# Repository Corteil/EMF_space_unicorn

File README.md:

# 🦄 Space Unicorn — EMF 2026 Hexpansion

A WS2812 NeoPixel hexpansion for the EMF Tildagon badge. An ATtiny85 setup as an I²C client
drives the LEDs with animated patterns, predefined colour palettes and a user
button for live pattern cycling. Settings can be saved to the ATtiny85's
internal EEPROM so the badge lights up on its own, without the control app.
This repository holds the firmware and the KiCad hardware design.

| Front | Rear |
|:-----:|:----:|
|  |  |

---

## Project links

The Space Unicorn is an EMF 2026 hexpansion — an ATtiny85 driving WS2812
NeoPixels, controlled over I²C from a Tildagon badge.

- 🦄 **Tildagon control app** — drive patterns, palettes, colour and speed from
  the badge: <https://github.com/Corteil/tildagon-space-unicorn>
- 📟 **This repo** — firmware (root) and the KiCad PCB design
  ([`hardware/`](hardware/)).
- 📇 **EMF hexpansion registry** — VID `0x1969` / PID `0x5355`, for OTA firmware:
  <https://github.com/emfcamp/hexpansion-firmwares/tree/main/0x1969/0x5355>

---

## Hardware

The full KiCad design (schematic, board, footprint libraries, gerbers and
renders) is in [`hardware/`](hardware/).

ATtiny85 pin assignments:

| Pin | Port     | Function                                      |
|-----|----------|-----------------------------------------------|
| 1   | PB5/RESET| Reset button                                  |
| 2   | PB3      | NeoPixel data output                          |
| 3   | PB4      | User button (active-low, internal pull-up)    |
| 4   | GND      |                                               |
| 5   | PB0      | I2C SDA                                       |
| 6   | PB1      | Heartbeat LED (1 Hz blink; flashes on I2C data)|
| 7   | PB2      | I2C SCL                                       |
| 8   | VCC      |                                               |

### Circuit

```
                        ^ VCC
                        |
    +--------+----------+----------+-----+-------+
    |        |                     |     |       |
    |       |"| 10k                |     |       |
    |       |_|                   |"| 10k |"| 10k
    |        |   +--ATtiny85--+   |_|   |_|
    |        +---| Reset  Vcc |----+     |
    |            |            |          |
  _____ 0.1u     |        SCL |----------+-------<> SCL
  _____  ,-------| GND    SDA |------------------<> SDA
    |    |       +------------+
    |    v GND
    |
    +---------------------------------------------------> NeoPixel Data (PB3)
    |
    +--[ button ]-- GND                                   User button (PB4)
    |
    +--[ LED ]--[ 330R ]-- GND                            Heartbeat LED (PB1)
```

Pull-ups: 10 kΩ on SCL, SDA and RESET to VCC.

---

## Building

Requires `avr-gcc`, `avr-libc`, and `avrdude`.

```bash
sudo apt install gcc-avr avr-libc binutils-avr avrdude

git clone --recurse-submodules https://github.com/Corteil/EMF_space_unicorn
cd EMF_space_unicorn

make fuses  # MUST be run once on any new or replacement chip
make        # build and flash
```

The default programmer is **Atmel-ICE (ISP)**. To use a different programmer
edit the top of `Makefile`:

```makefile
AVRDUDE_PROGRAMMER = usbasp     # or linuxspi, avrisp2, usbtiny, ...
AVRDUDE_PORT       = usb
```

Build artifacts (`main.hex`, `main.elf`) are not tracked in the repository —
always build from source so the hex matches the current code.

### Fuses — required on every fresh chip

> **Important:** ATtiny85 chips ship from the factory with `CKDIV8` programmed,
> running the CPU at 1 MHz. The WS2812 driver requires exactly 8 MHz. With the
> wrong clock the NeoPixels will be **stuck solid white** and the button will be
> unresponsive.
>
> Run `make fuses` once whenever fitting a new or replacement chip. This sets
> `LFUSE=0xE2` (8 MHz internal RC, no divider) and is safe to re-run on a
> chip that is already correctly programmed.

---

## Flash and RAM usage

| Section | Used    | Available |
|---------|---------|-----------|
| Flash   | 3708 B  | 8192 B    |
| RAM     | 390 B   | 512 B     |

---

## I2C Protocol

**Slave address: 0x40** (hardcoded in `i2c/i2c_slave_defs.h`)

The full 8-bit register space (0x00–0xFF) is addressable.

Write transaction:

| Start | Addr (0x40) | Register | Data bytes… | Stop |

Read transaction:

| Start | Addr (0x40) | Register | Restart | Addr (0x41) | Data bytes… | Stop |

The register address auto-increments after each byte, so multi-byte reads and
writes are supported in a single transaction.

**LED values are updated only after a STOP condition is received.** There is
no per-LED frame buffer — each pixel is computed on the fly as the WS2812
stream is clocked out, so LED count is limited by power and frame rate, not
by RAM.

---

## Register Map

| Address     | Name           | Description                                    | Reset |
|-------------|----------------|-------------------------------------------------|-------|
| 0x00        | **CTRL**       | Control register                                | 0x00  |
| 0x01        | **PATTERN**    | Pattern ID (0–10, see table below)              | 0x01  |
| 0x02        | **SPEED**      | Ticks per animation frame (1=fast, 255=slow)    | 0x0A  |
| 0x03        | **FALLBACK**   | Pattern ID run on boot / after an idle timeout  | 0x07  |
| 0x04        | **N_LEDS_LO**  | Active LED count, low byte                      | 0x40  |
| 0x05        | **N_LEDS_HI**  | Active LED count, high byte                     | 0x00  |
| 0x06        | **N_COLS**     | Matrix columns for RAINBOW_MTX (0 ⇒ 8)          | 0x08  |
| 0x07        | **IDLE_TO**    | Inactivity timeout in seconds before reverting to FALLBACK (0=off) | 0x00 |
| 0x08        | **PARAM1**     | Pattern-specific parameter                      | 0x01  |
| 0x09        | **PARAM2**     | Pattern-specific parameter                      | 0x05  |
| 0x0A        | **PAL_SEL**    | Palette selector (0=user, 1–7=predefined)       | 0x00  |
| 0x10        | **GLB_G**      | Primary colour — green                          | 0x00  |
| 0x11        | **GLB_R**      | Primary colour — red                            | 0xFF  |
| 0x12        | **GLB_B**      | Primary colour — blue                           | 0x00  |
| 0x13        | **SEC_G**      | Secondary colour — green                        | 0x00  |
| 0x14        | **SEC_R**      | Secondary colour — red                          | 0x00  |
| 0x15        | **SEC_B**      | Secondary colour — blue                         | 0x00  |
| 0x20–0x4F   | **PALETTE[0–15]** | 16-entry user colour palette, 3 bytes (G,R,B) each | 0x00 |
| 0x50–0xFF   | **INDEX[0–351]**  | Packed 4-bit palette-index buffer for matrix mode (see below) | 0x00 |

`N_LEDS_LO`/`N_LEDS_HI` form a 16-bit active LED count (little-endian); a
value of 0 is treated as 64. `PATTERN`, `SPEED`, `PARAM1`/`PARAM2` and colours
are unchanged in meaning from earlier firmware, but have moved address.

> WS2812 byte order on the wire is **G, R, B**.

---

## CTRL Register (0x00)

| Bit | Name       | Description |
|-----|------------|-------------|
| 0   | **RST**    | Write 1 to reset all registers to defaults. Auto-clears. |
| 1   | **GLB**    | Write 1 to display the primary colour (GLB_G/R/B) on all LEDs. |
| 2   | **PAT_EN** | Write 1 to enable the pattern animation engine. |
| 3   | **IDX_EN** | Write 1 to stream LED colours from the packed index buffer (0x50–0xFF) instead of a pattern. |
| 4   | **SAVE**   | Write 1 to persist the current configuration to EEPROM. Auto-clears once saved. |
| 7–5 | —          | Reserved, read as 0. |

---

## Patterns (REG_PATTERN, 0x01)

| ID | Name            | Description                                                   | Uses |
|----|-----------------|---------------------------------------------------------------|------|
| 0  | OFF             | All LEDs off                                                  | —           |
| 1  | SOLID           | All LEDs show primary colour                                  | —           |
| 2  | CHASE           | Scrolling comet; tail dims by right-shift, capped at 1/128    | PARAM1 = tail length |
| 3  | BLINK           | All LEDs toggle between primary and off                       | —           |
| 4  | ALTERNATE       | Even LEDs = primary, odd = secondary; swaps each frame        | —           |
| 5  | WIPE            | Fill left→right one LED per frame, then clear                 | —           |
| 6  | TWINKLE         | Independently-timed sparkles fade in/out at random LEDs       | PARAM1 = number of simultaneous sparkles (max 8) |
| 7  | RAINBOW         | Full hue wheel cycling across the strip                       | PARAM2 = hue step per LED |
| 8  | RAINBOW_MTX     | Diagonal rainbow on an N_COLS-wide grid, rotates over time     | PARAM1 bit 0 = serpentine wiring |
| 9  | RETRO_BLINK     | Random LEDs toggle independently (50s computer effect); state kept for the first 512 LEDs only | PARAM1 = LEDs toggled per frame (max 8) |
| 10 | LARSON          | Cylon/KITT scanner; bright eye bounces end-to-end, tail dims same as CHASE | PARAM1 = tail length |

Enable a pattern by writing PAT_EN to CTRL and the ID to PATTERN. The user
button (PB4) also cycles through patterns 1–10 with a single press.

---

## Predefined Palettes (REG_PAL_SEL, 0x0A)

Writing a palette ID loads predefined primary and secondary colours from flash
(PROGMEM) into GLB and SEC registers. Writing 0 keeps the current user colours.

| ID | Name    | Primary (G R B)   | Secondary (G R B) |
|----|---------|-------------------|-------------------|
| 0  | USER    | *(unchanged)*     | *(unchanged)*     |
| 1  | FIRE    | 100, 255, 0       | 0, 128, 0         |
| 2  | OCEAN   | 255, 0, 255       | 0, 0, 64          |
| 3  | FOREST  | 200, 50, 0        | 48, 10, 0         |
| 4  | PARTY   | 0, 255, 0         | 0, 0, 255         |
| 5  | MONO_W  | 255, 255, 255     | 32, 32, 32        |
| 6  | RAINBOW | 0, 255, 0         | 0, 0, 255         |
| 7  | HEAT    | 0, 255, 0         | 200, 255, 0       |

---

## User Palette and Index Buffer (matrix mode)

Setting `CTRL_IDX_EN` switches LED output from the pattern engine to a
directly-addressable canvas, driven by two blocks:

- **`PALETTE[0–15]`** (0x20–0x4F) — 16 user-defined colours, 3 bytes (G, R, B)
  each. On reset, entries 0 and 1 are set to the primary/secondary colours;
  all 16 entries can be freely overwritten over I2C.
- **`INDEX[0–351]`** (0x50–0xFF) — one 4-bit palette index per LED, two LEDs
  packed per byte (LED *n*'s index is the low nibble of byte `n/2` if *n* is
  even, the high nibble if odd). Index **0 always renders as off/blank**,
  regardless of palette contents; indices 1–15 select `PALETTE[1]`…`PALETTE[15]`.

Index mode is bounded by the size of the index buffer: 176 bytes × 2 LEDs per
byte = **352 LEDs maximum**, irrespective of `N_LEDS`.

---

## Persistence, Fallback and Idle Timeout

- **Save**: writing `CTRL_SAVE` copies the control/colour registers and the
  16-entry user palette into the ATtiny85's internal EEPROM. The bit
  auto-clears once the save completes.
- **Boot**: on power-up, a valid saved configuration is reloaded; otherwise
  firmware defaults are used. The badge then runs the `FALLBACK` pattern
  immediately, so it lights up without the control app.
- **Idle timeout**: if `IDLE_TO` is non-zero and no I2C write is seen for that
  many seconds, the firmware reverts to the `FALLBACK` pattern.

---

## Heartbeat LED (PB1)

The LED on PB1 serves two purposes:

- **Heartbeat**: slow blink while the firmware is running, driven by Timer0 ISR.
- **Data activity**: overrides the heartbeat with a brief solid-on flash each
  time an I2C STOP condition is received.

---

## Testing

`test_registers.py` is a MicroPython / Raspberry Pi dual-platform test tool
that verifies all registers over I2C.

**Raspberry Pi (Linux):**
```bash
sudo apt install python3-smbus2
python3 test_registers.py
```

**Pi Pico (MicroPython):**
```
# Copy test_registers.py to the Pico, then run from the REPL or Thonny.
# Edit MP_PIN_SDA / MP_PIN_SCL at the top of the file to match your wiring.
mpremote run test_registers.py
```

The tool provides an interactive menu for running automated register tests and
live control of patterns, palettes, colours, and individual LEDs.

---

## Acknowledgements

This firmware extends
[neopixel_i2c](https://github.com/usedbytes/neopixel_i2c) by
**Brian Starkey (usedbytes)**, which provides the USI I2C slave implementation
and the original WS2812 driving code. The WinAVR Makefile was written by
**Eric B. Weddington, Jörg Wunsch et al.** and modified by **Elliot Williams**.
The [light_ws2812](https://github.com/cpldcpu/light_ws2812) library by
**cpldcpu** is used for WS2812 output.

---

---

# Original README — neopixel_i2c (picopixel)

> The following is the original README from the upstream neopixel_i2c project
> by Brian Starkey (usedbytes), preserved for reference.

This is an AVR-based neopixel driver. It accepts commands over i2c to drive a
a number of ws2812 LED pixels.

The code on the master branch is set up for an Attiny85, with the LEDs on PB3,
using an usbasp programmer. The fuses should be set to use 8 MHz internal
oscillator, **no divider**

## How many LEDs?
The number of LEDs is currently hardcoded in the firmware. The maximum number
depends on the amount of RAM available on your AVR.
An Attiny45 should be able to drive 82 LEDs, and an Attiny85, 167.

## Circuit

Suggested circuit.

```
                            ^ VCC
                            |
    +--------+--------------+-------------+-----+-------+
    |        |                            |     |       |
    |       |"| 10k                       |     |       |
    |       |_|                           |     |       |
    |        |     +Attinyx5--------+     |    |"| 2k2 |"| 2k2
    |        +-----| Reset      Vcc |-----'    |_|     |_|
    |              |                |           |       |
  _____ 0.1u       |                |           |       |
  _____  ,---------|            SCL |-----------+-------|-----<> SCL
    |    |         |                |                   |
    |    |         |                |                   |
    |    |       --|                |--                 |
    |    |         |                |                   |
    |    |         |                |                   |
    +----|---+-----| GND        SDA |-------------------+-----<> SDA
         |   |     +----------------+
         |   v GND
         |
         '-----------------------------------------------------> NeoPixel Data

```

## Getting the code

This project uses git submodules (I kinda wish it didn't...). You can clone
it like so:

```git clone --recursive https://github.com/usedbytes/neopixel_i2c```

If your git version is too old to support that, do this instead:

```
git clone --recursive https://github.com/usedbytes/neopixel_i2c
cd neopixel_i2c
git submodule update --init --recursive
```

## Basic Functionality

There are two basic operating modes:
 * In *normal* mode, each LED is individually driven based on the value in its
   control register.
 * In *global* mode, all LEDs are driven to the same value, based on the values
   in the global value registers.

The operating modes are selected by flipping the *GLB* bit in the **CTRL**
register.

## i2c Protocol

**The slave address is currently hardcoded to 0x40 in the firmware**, see

```
i2c/i2c_slave_defs.h:30
```

This utilises my i2c slave library (https://github.com/usedbytes/usi_i2c_slave)
which means it follows a fairly standard i2c protocol (for more, see here:
http://www.robot-electronics.co.uk/i2c-tutorial).

Writes look like this:

| Start | Slave Address << 1 | Register Address | Data | Stop |
|-------|--------------------|------------------|------|------|

The register address will auto-increment after every byte, so you can write
data in bursts.

Reads look like this:

| Start | Slave Address | Register Address | Restart | (Slave Address << 1) + 1  | Data | Stop |
|-------|---------------|------------------|---------|---------------------------|------|------|

First you do a write transaction to set the register address to read from, then
a read transaction to read the data. When you've read all the data you want,
send a NAK after the last byte to terminate the read.

**The LED values are only updated after a STOP is received**

## Register Map
The register map consists of a number of global control registers - address
0x0-0x3 - followed by an array of registers which hold the individual value
for each LED in normal mode.

| **Address** | **Name**     | **Description**      | **Access** | **Reset** |
|------------:|--------------|:---------------------|--------|------:|
|   0x00      | **CTRL**     | Control Register     | R/W    |    0  |
|   0x01      | **GLB_G**    | Global Green Value   | R/W    |    0  |
|   0x02      | **GLB_R**    | Global Red Value     | R/W    |    0  |
|   0x03      | **GLB_B**    | Global Blue Value    | R/W    |    0  |
|Array follows|--------------|----------------------|--------|-------|
|   0x04      | **GREEN[0]** | Green value, LED0    | R/W    |    0  |
|   0x05      | **RED[0]**   | Red value, LED0      | R/W    |    0  |
|   0x06      | **BLUE[0]**  | Blue value, LED0     | R/W    |    0  |
|   ....      | ....         | ....                 | ....   | ....  |
| (3*n) + 4   | **GREEN[n]** | Green value, LEDn    | R/W    |    0  |
| (3*n) + 5   | **RED[n]**   | Red value, LEDn      | R/W    |    0  |
| (3*n) + 6   | **BLUE[n]**  | Blue value, LEDn     | R/W    |    0  |

## Register Descriptions

### **CTRL**
The control register sets the operating mode.

|   Name: | RSVD | RSVD | RSVD | RSVD | RSVD | RSVD | GLB  | RST  |
|--------:|:----:|:----:|:----:|:----:|:----:|:----:|:----:|:----:|
|    Bit: |    7 |    6 |    5 |    4 |    3 |    2 |    1 |    0 |
| Access: |    r |    r |   r  |   r  |   r  |   r  |  rw  |  rw  |

#### *RST*
Writing a 1 to this bit will reset the LED controler, setting all LEDs to OFF

This bit will be automatically cleared once the reset has completed.

#### *GLB*
Writing a one to this bit causes the global color value to be displayed on all
LEDs at the end of the transaction - Normally you would set the **GLB_R**,
**GLB_G**, and **GLB_B** values in the same transaction as setting the *GLB*
bit so that the new colour is immediately applied.

Writing a zero to this bit will disable the global colour override and return to
normal operation.

### **GLB_R**, **GLB_G**, **GLB_B**
These registers hold the global colour value. When the *GLB* bit in the
**CTRL** register is set, all LEDs will display this colour.

### **LED Value Array**
Everything after the global registers is an array of data for each LED.
When the *GLB* bit is not set, each LED will display whatever value is
programmed in its corresponding register set.

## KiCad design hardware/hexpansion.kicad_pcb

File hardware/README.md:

# Space Unicorn — hardware

KiCad design files for the EMF26 Space Unicorn hexpansion.

| Front | Rear |
|:-----:|:----:|
|  |  |

## Contents

| Path | What |
|------|------|
| `hexpansion.kicad_pro` / `.kicad_sch` / `.kicad_pcb` | KiCad project, schematic and board. |
| `fp-lib-table`, `sym-lib-table` | Library tables. |
| `*.pretty/` | Project-local footprint libraries (`unicorn`, `heart`, `gfx`, `NextPCB`). |
| `gerbers/` | Gerbers + drill files for fabrication. |
| `renders/` | Board renders and the paper template. |
| `LICENSE.txt` | Hardware licence. |

## Notes

- The board carries an **ATtiny85** (WS2812 driver, I²C `0x40`), an **M24256E**
  EEPROM (hexpansion identity + resident app), and a **BC857BS** for Ext_5V
  reverse-feed protection.
- `fp-lib-table` references some footprints by absolute local paths (parts from
  `…/Hardware/parts/…`) and a sibling `tildagon-base`. These won't resolve on a
  fresh clone, but KiCad **caches footprints in the `.kicad_pcb`**, so the board
  opens, views and plots correctly. Re-point those library entries if you need to
  edit footprints.

## Related

- Firmware: this repository's root.
- Tildagon control app: <https://github.com/Corteil/tildagon-space-unicorn>

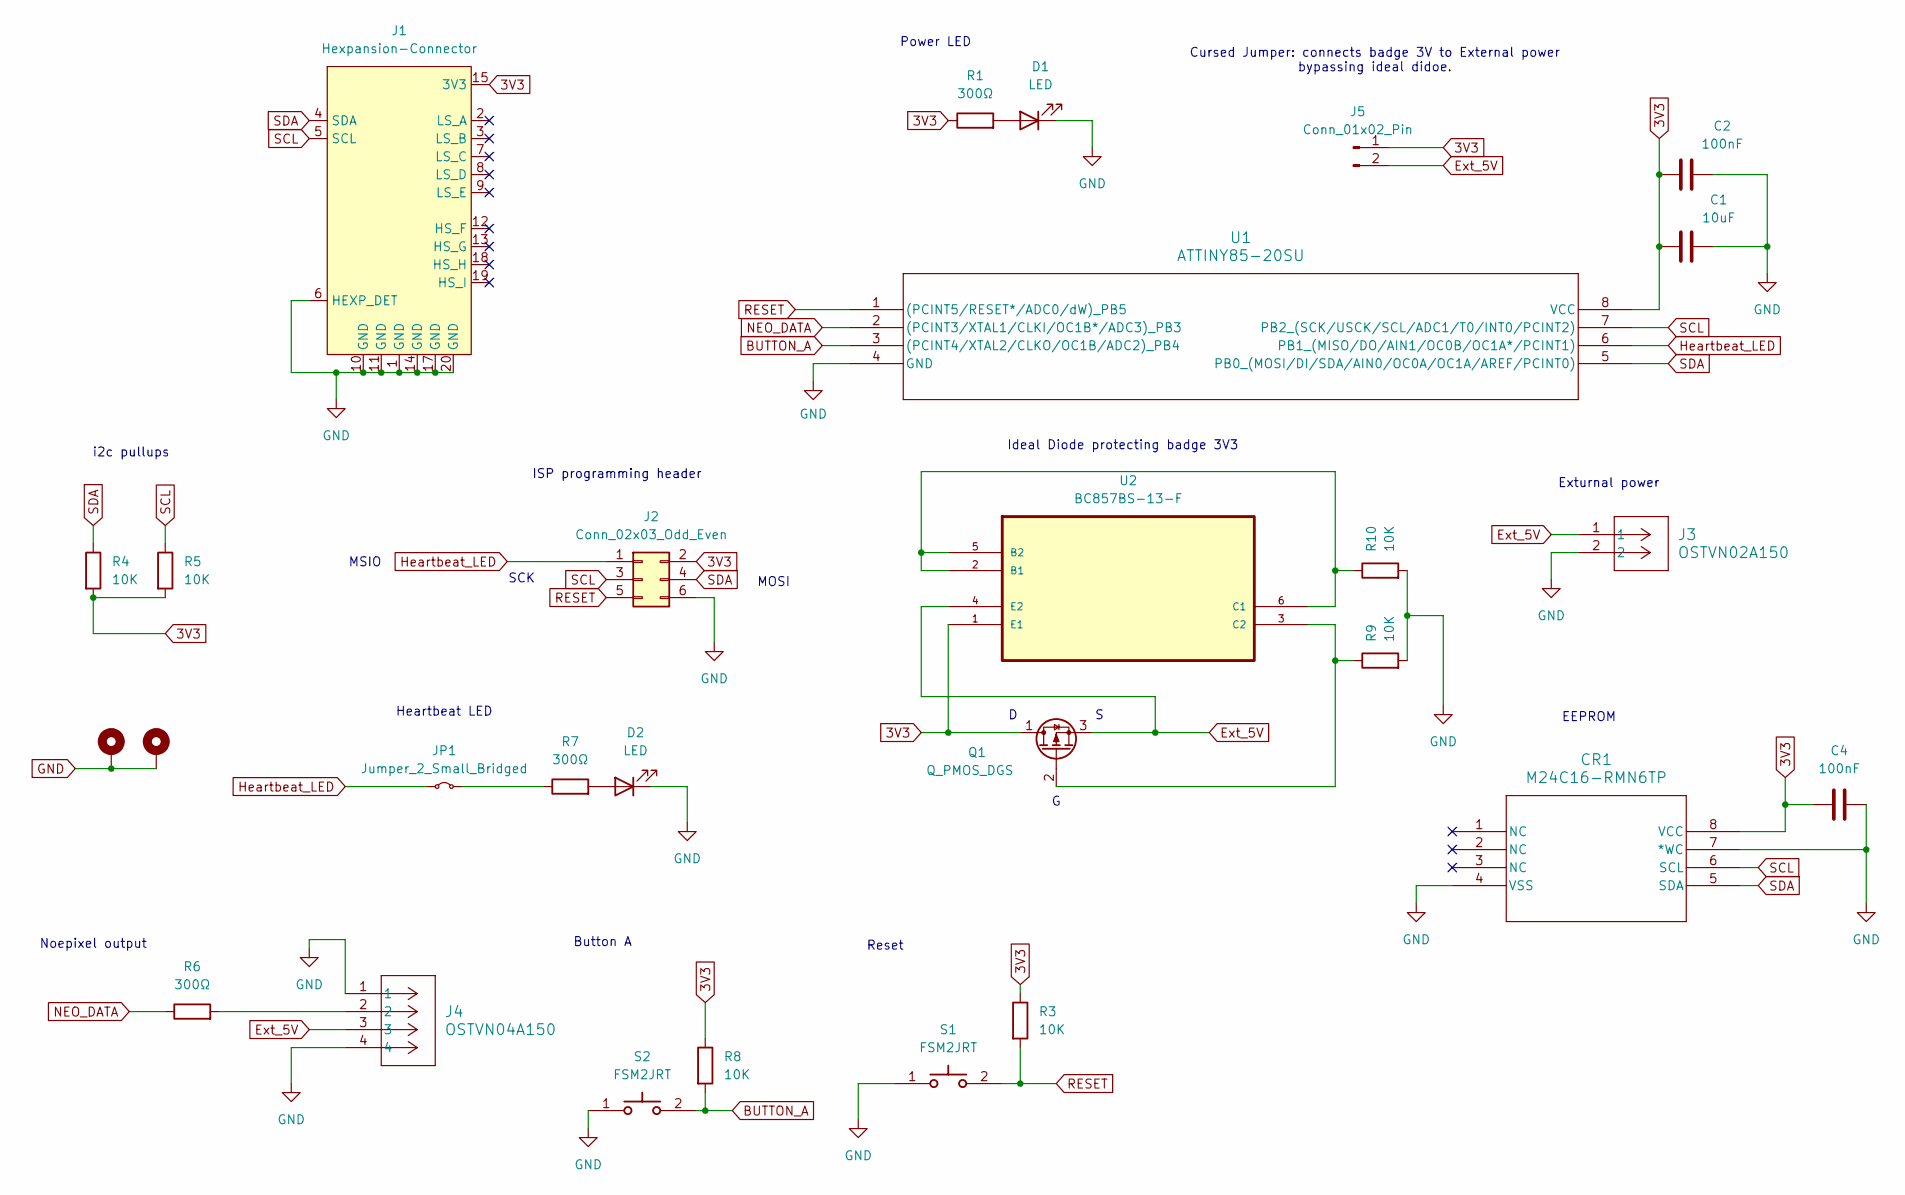
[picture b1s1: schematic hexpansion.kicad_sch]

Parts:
C1: 10uF; C_0603_1608Metric_Pad1.08x0.95mm_HandSolder
C2, C4: 100nF; C_0603_1608Metric_Pad1.08x0.95mm_HandSolder
CR1: M24C16-RMN6TP; SO-8_STM
D1, D2: LED; LED_0805_2012Metric
H1, H2: MountingHole_Pad; MountingHole_2.2mm_M2_Pad_Via
J1: Hexpansion-Connector; hexpansion-edge-connector
J2: Conn_02x03_Odd_Even; PinHeader_2x03_P2.54mm_Vertical
J3: OSTVN02A150; CONN_OSTVN02A150_OST
J4: OSTVN04A150; CONN_OSTVN04A150_OST
J5: Conn_01x02_Pin; PinHeader_1x02_P2.54mm_Vertical
JP1: Jumper_2_Small_Bridged; SolderJumper-2_P1.3mm_Bridged2Bar_RoundedPad1.0x1.5mm
Q1: Q_PMOS_DGS; SOT-23
R1, R6, R7: 300Ω; R_0603_1608Metric
R3, R4, R5, R8, R9, R10: 10K; R_0603_1608Metric
S1, S2: FSM2JRT; Manufacturer_Part_Number FSM2JRT
U1: ATTINY85-20SU; 8S2_ATM
U2: BC857BS-13-F; SOT65P210X100-6N; MPN BC857BS-13-F

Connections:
3V3: C1.1, C2.1, C4.1, CR1.8 (VCC), J1.15 (3V3), J1.16 (3V3), J2.2, J5.1, Q1.1 (D), R1.1, R3.1, R4.2, R5.2, R8.1, U1.8 (VCC), U2.1 (E1)
BUTTON_A: R8.2, S2.2 (NO), U1.3 ((PCINT4/XTAL2/CLKO/OC1B/ADC2)_PB4)
Ext_5V: J3.1, J4.3, J5.2, Q1.3 (S), U2.4 (E2); also elsewhere on the board
GND: C1.2, C2.2, C4.2, CR1.4 (VSS), CR1.7 (*WC), D1.1 (K), D2.1 (K), H1.1 (1_1), H2.1 (1_1), J1.1 (GND), J1.6 (HEXP_DET), J1.10 (GND), J1.11 (GND), J1.14 (GND), J1.17 (GND), J1.20 (GND), J2.6, J3.2, J4.1, J4.4, R9.2, R10.2, S1.1 (COM), S2.1 (COM), U1.4 (GND); also elsewhere on the board
Heartbeat_LED: J2.1, JP1.1 (A), U1.6 (PB1_(MISO/DO/AIN1/OC0B/OC1A*/PCINT1))
NEO_DATA: R6.1, U1.2 ((PCINT3/XTAL1/CLKI/OC1B*/ADC3)_PB3)
unnamed: D1.2 (A), R1.2
unnamed: D2.2 (A), R7.2
unnamed: J4.2, R6.2
unnamed: JP1.2 (B), R7.1
unnamed: Q1.2 (G), R9.1, U2.3 (C2)
unnamed: R10.1, U2.2 (B1), U2.5 (B2), U2.6 (C1)
RESET: J2.5, R3.2, S1.2 (NO), U1.1 ((PCINT5/RESET*/ADC0/dW)_PB5)
SCL: CR1.6 (SCL), J1.5 (SCL), J2.3, R5.1, U1.7 (PB2_(SCK/USCK/SCL/ADC1/T0/INT0/PCINT2))
SDA: CR1.5 (SDA), J1.4 (SDA), J2.4, R4.1, U1.5 (PB0_(MOSI/DI/SDA/AIN0/OC0A/OC1A/AREF/PC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)

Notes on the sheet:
Power LED
Exturnal power
Heartbeat LED
Noepixel output
MSIO
EEPROM
MOSI
ISP programming header
SCK
Reset
Button A
Cursed Jumper: connects badge 3V to External power bypassing ideal didoe.
Ideal Diode protecting badge 3V3
i2c pullups

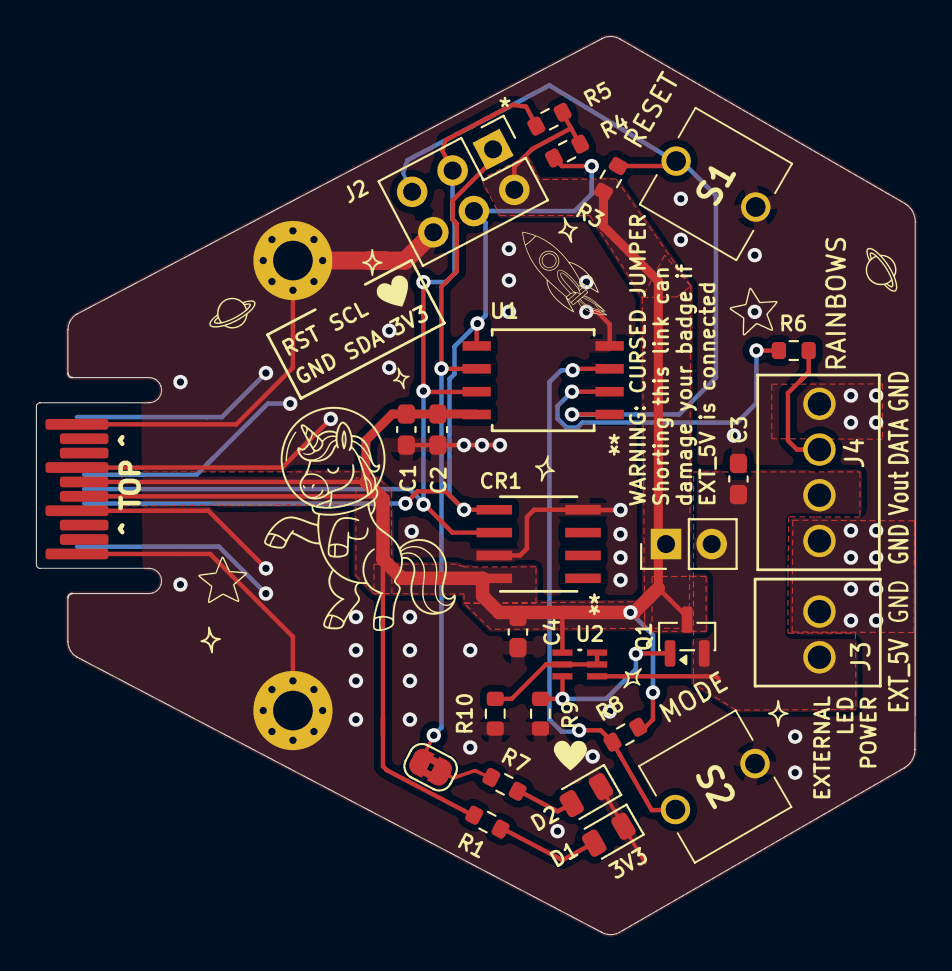
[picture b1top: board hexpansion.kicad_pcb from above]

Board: 2 copper layers, 48.8 x 49.9 mm, 29 parts (0 on the bottom side), 15 nets.

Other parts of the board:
C3: 100nF; C_0603_1608Metric_Pad1.08x0.95mm_HandSolder

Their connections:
Ext_5V: C3.1; also elsewhere on the board
GND: C3.2; also elsewhere on the board
